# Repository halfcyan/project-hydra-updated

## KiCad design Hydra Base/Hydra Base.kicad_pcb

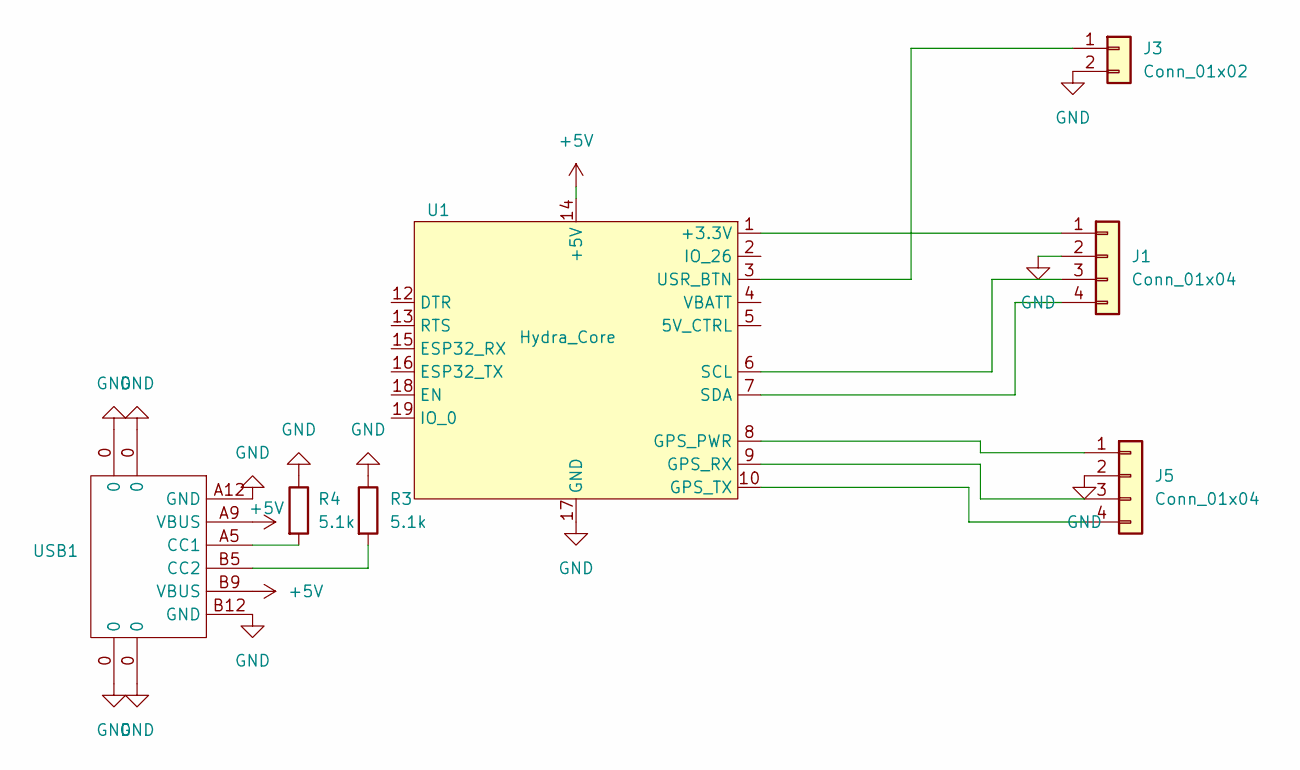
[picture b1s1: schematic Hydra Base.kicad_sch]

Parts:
J1, J5: Conn_01x04; PinHeader_1x04_P2.54mm_Vertical
J3: Conn_01x02; PinHeader_1x02_P2.54mm_Vertical
R3, R4: 5.1k; R_Axial_DIN0204_L3.6mm_D1.6mm_P5.08mm_Horizontal
U1: Hydra_Core; Hydra_core
USB1: USB-C-SMD_TYPE-603-T3

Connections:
+5V: U1.14 (+5V), USB1.A9 (VBUS), USB1.B9 (VBUS)
GND: J1.2, J3.2, J5.2, R3.1, R4.1, U1.11 (GND), U1.17 (GND), USB1.0, USB1.A12 (GND), USB1.B12 (GND)
unnamed: J1.1, U1.1 (+3.3V)
unnamed: J1.3, U1.6 (SCL)
unnamed: J1.4, U1.7 (SDA)
unnamed: J3.1, U1.3 (USR_BTN)
unnamed: J5.1, U1.8 (GPS_PWR)
unnamed: J5.3, U1.9 (GPS_RX)
unnamed: J5.4, U1.10 (GPS_TX)
unnamed: R4.2, USB1.A5 (CC1)
unnamed: R3.2, USB1.B5 (CC2)

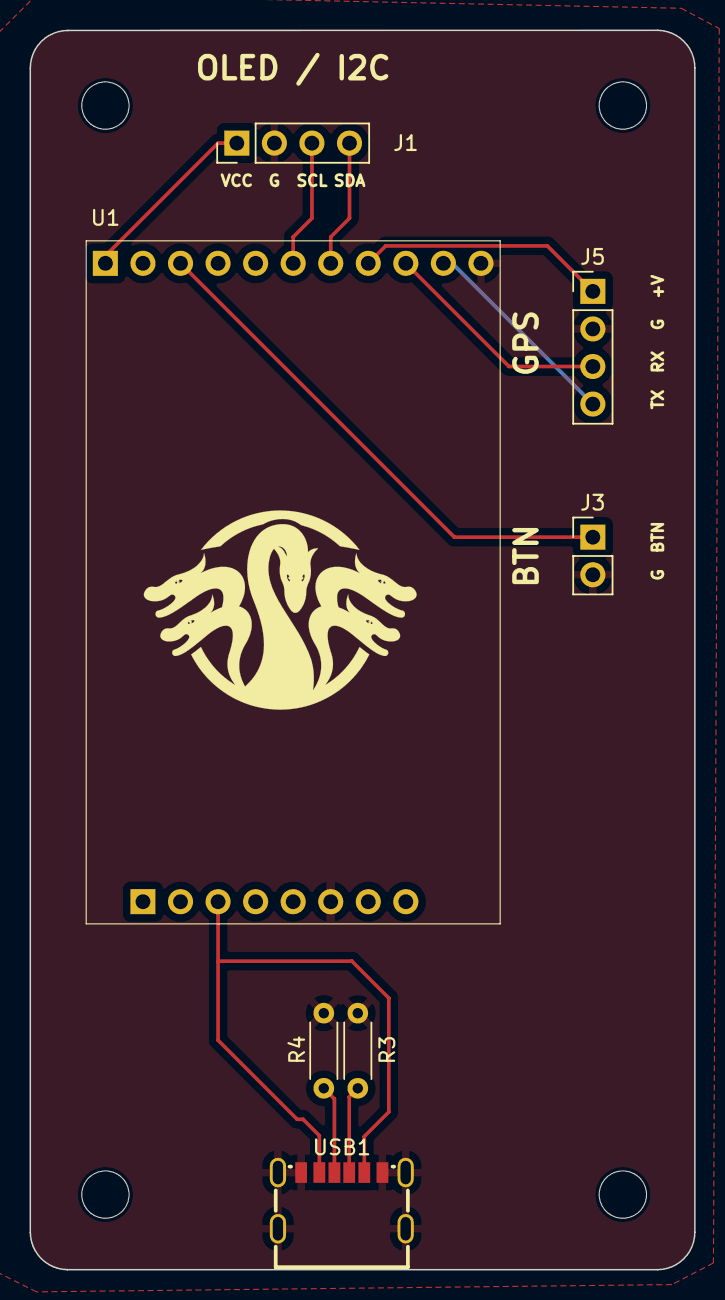
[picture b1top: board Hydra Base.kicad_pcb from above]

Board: 2 copper layers, 45.0 x 83.8 mm, 7 parts (0 on the bottom side), 11 nets.

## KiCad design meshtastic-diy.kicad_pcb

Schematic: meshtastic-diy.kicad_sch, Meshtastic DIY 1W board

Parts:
C1, C2, C4, C5: 100n; C_0603_1608Metric; LCSC# C519438
C3, C10, C11, C12, C13: 22uF; C_0603_1608Metric; LCSC# C86295
C6: 100n; C_0603_1608Metric
D1: LED; LED_0603_1608Metric; LCSC# C434421
H2, H3: tooling_hole; jlc_toolinghole
J1: programming header; PinHeader_1x08_P2.54mm_Vertical
J2: oled/gps/external HW; PinHeader_1x11_P2.54mm_Vertical
J4: ipex antenna; U.FL_Molex_MCRF_73412-0110_horizontal; LCSC# C882052
L2: 4.7uH; L_Chilisin_BMRA00040420; LCSC# C136097
NT1: Net-Tie_2; NetTie-2_SMD_Pad0.5mm
Q1, Q2, Q4: BC848; SOT-23; LCSC# C8577
Q5: CJ2301; SOT-23; LCSC# C8547
R1, R8: 470; R_0603_1608Metric; LCSC# C23179
R2, R10, R11, R16: 0; R_0603_1608Metric; LCSC# C15402
R3, R4, R5, R6, R7, R9, R12, R15, R17: 10k; R_0603_1608Metric; LCSC# C98220
R13: 536k; R_0603_1608Metric; LCSC# C227955
R14: 118k; R_0603_1608Metric; LCSC# C137804
SYM1: Meshtastic Logo; meshtastic_logo
TP1, TP2: TestPoint; TestPoint_Pad_D1.0mm
U1: ESP32-WROOM-32UE-N8; ESP32WROOM32UEN8; Manufacturer_Part_Number ESP32-WROOM-32UE-N8; Mouser Part Number 356-ESP32WRM32UE64UH
U2: ESP-PSRAM64; SOIC-8_3.9x4.9mm_P1.27mm; LCSC# C261881
U3: E22-900M30S; e22-900m30s-handsoldering; LCSC# C411294
U5: PAM2312; SOT-23-5; LCSC# C157537

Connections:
+3.3V: C2.1, C3.1, C4.1, C11.1, C12.1, L2.2, R5.2, R6.2, R7.1, R9.2, R10.2, R13.1, U1.2 (3V3), U2.8 (VCC)
+5V: C5.1, C10.1, C13.1, R11.2, U3.9 (VCC), U3.10 (VCC), U5.1 (EN), U5.4 (VIN)
/5V_pwrctrl: U1.10 (IO25)
/DTR: Q1.2 (E), R4.1
/EN: C1.1, Q2.3 (C), R7.2, U1.3 (EN)
/ESP32_RX: R1.1, U1.34 (RXD0)
/ESP32_TX: R2.1, U1.35 (TXD0)
/GPIO0: Q1.3 (C), R5.1, U1.25 (IO0)
/GPIO2: D1.2 (A), U1.24 (IO2)
/GPIO16: R6.1, U1.27 (IO16), U2.1 (~CE)
/GPS_PWR_enable: R12.1, R16.2, R17.2, U1.26 (IO4)
/GPS_RX: U1.14 (IO12)
/GPS_TX: U1.23 (IO15)
/GPS_pwr: Q5.3 (D), R16.1
/RTS: Q2.2 (E), R3.1
/SCL: U1.36 (IO22)
/SDA: U1.33 (IO21)
/SDI_SD1: U1.22 (NC_6), U2.5 (SI/SIO)
/SDO_SD0: U1.21 (NC_5), U2.2 (SO/SIO)
/SHD_SD2: U1.17 (NC_1), U2.7 (SIO3)
/SRAM_CLK: U1.28 (IO17), U2.6 (SCLK)
/SWP_SD3: U1.18 (NC_2), U2.3 (SIO2)
/USR_BTN: R9.1, U1.5 (SENSOR_VN)
/e22_BUSY: U1.8 (IO32), U3.14 (BUSY)
/e22_DIO1: U1.9 (IO33), U3.13 (DIO1)
/e22_MISO: U1.31 (IO19), U3.16 (MISO)
/e22_MOSI: U1.12 (IO27), U3.17 (MOSI)
/e22_NRST: U1.37 (IO23), U3.15 (NRST)
/e22_NSS: U1.30 (IO18), U3.19 (NSS)
/e22_RXEN: U1.13 (IO14), U3.6 (RXEN)
/e22_SCK: U1.29 (IO5), U3.18 (SCK)
/e22_TXEN: U1.16 (IO13), U3.7 (TXEN)
/gpio_26: U1.11 (IO26)
/vbat_mon: C6.1, U1.7 (IO35)
GND: C1.2, C2.2, C3.2, C4.2, C5.2, C6.2, C13.2, J4.2 (Ext), Q4.2 (E), R8.2, R17.1, U1.1 (GND_1), U1.15 (GND_2), U1.38 (GND_3), U1.39 (GND_4), U1.40 (GND_5), U1.41 (GND_6), U1.42 (GND_7), U1.43 (GND_8), U1.44 (GND_9), U1.45 (GND_10), U1.46 (GND_11), U1.47 (GND_12), U2.4 (VSS), U3.1 (GND), U3.2 (GND), U3.3 (GND), U3.4 (GND), U3.5 (GND), U3.11 (GND), U3.12 (GND), U3.20 (GND), U3.22 (GND)
GNDA: C10.2, C11.2, C12.2, R14.2, U5.2 (GND)
unnamed: D1.1 (K), R8.1
unnamed: J4.1 (In), U3.21 (ANT)
unnamed: Q1.1 (B), R3.2
unnamed: Q2.1 (B), R4.2
unnamed: Q4.1 (B), R12.2
unnamed: Q4.3 (C), Q5.1 (G), R15.1
unnamed: Q5.2 (S), R10.1, R11.1, R15.2
unnamed: TP2.1, U1.6 (IO34)
unnamed: TP1.1, U1.4 (SENSOR_VP)
unnamed: R13.2, R14.1, U5.5 (FB)
unnamed: L2.1, U5.3 (SW)

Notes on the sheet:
GPIO option
PSRAM option
Auto reset option
5V/3.3V option
status LED

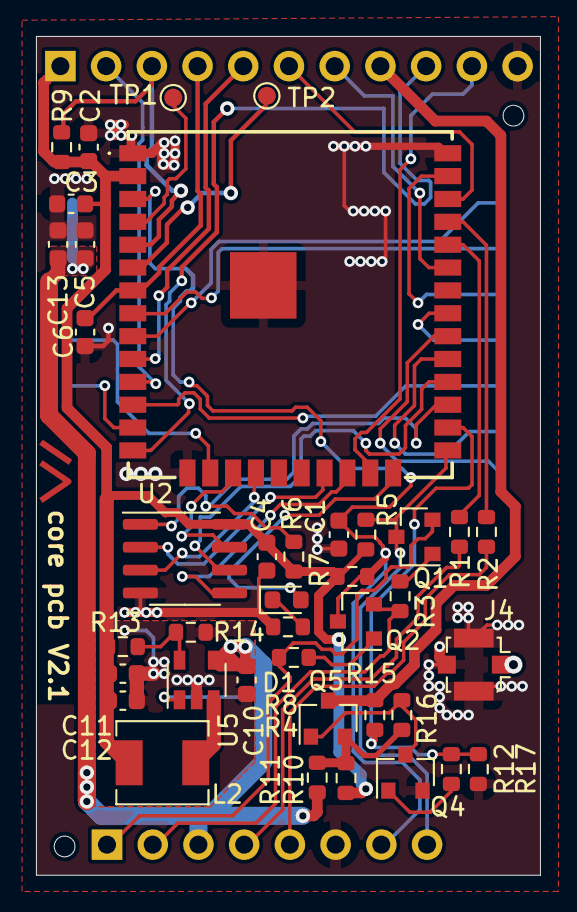
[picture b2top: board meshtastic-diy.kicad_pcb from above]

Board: 2 copper layers, 28.0 x 46.6 mm, 43 parts (1 on the bottom side), 41 nets.

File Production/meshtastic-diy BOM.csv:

"Id";"Designator";"Footprint";"Quantity";"Designation";"Supplier and ref";
1;"Q1,Q2,Q4";"SOT-23";3;"BC848";;;
2;"R1,R8";"R_0603_1608Metric";2;"470";;;
3;"U2";"SOIC-8_3.9x4.9mm_P1.27mm";1;"ESP-PSRAM64";;;
4;"C4,C5,C6,C1,C2";"C_0603_1608Metric";5;"100n";;;
5;"L2";"L_Chilisin_BMRA00040420";1;"4.7uH";;;
6;"R3,R6,R9,R4,R7,R5,R15,R12,R17";"R_0603_1608Metric";9;"10k";;;
7;"R2,R16,R10,R11";"R_0603_1608Metric";4;"0";;;
8;"D1";"LED_0603_1608Metric";1;"LED";;;
9;"R14";"R_0603_1608Metric";1;"118k";;;
10;"C10,C12,C13,C3,C11";"C_0603_1608Metric";5;"22uF";;;
11;"H2,H3";"jlc_toolinghole";2;"tooling_hole";;;
12;"J4";"U.FL_Molex_MCRF_73412-0110_horizontal";1;"ipex antenna";;;
13;"SYM1";"meshtastic_logo";1;"Meshtastic Logo";;;
14;"TP1,TP2";"TestPoint_Pad_D1.0mm";2;"TestPoint";;;
15;"R13";"R_0603_1608Metric";1;"536k";;;
16;"U5";"SOT-23-5";1;"PAM2312";;;
17;"Q5";"SOT-23";1;"CJ2301";;;
18;",,,,,,,,,,,,,,,,,,";"";19;"";;;
19;"U1";"ESP32WROOM32UEN8";1;"ESP32-WROOM-32UE-N8";;;
20;"U3";"e22-900m30s-handsoldering";1;"E22-900M30S";;;

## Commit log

2024-04-17 Update hardware files
